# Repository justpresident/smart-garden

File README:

smart-garden
============

Automatic watering system for your garden or home plants

The systems consists of Arduino-compatible AVR microcontroller connected to basic lcd and water pump.

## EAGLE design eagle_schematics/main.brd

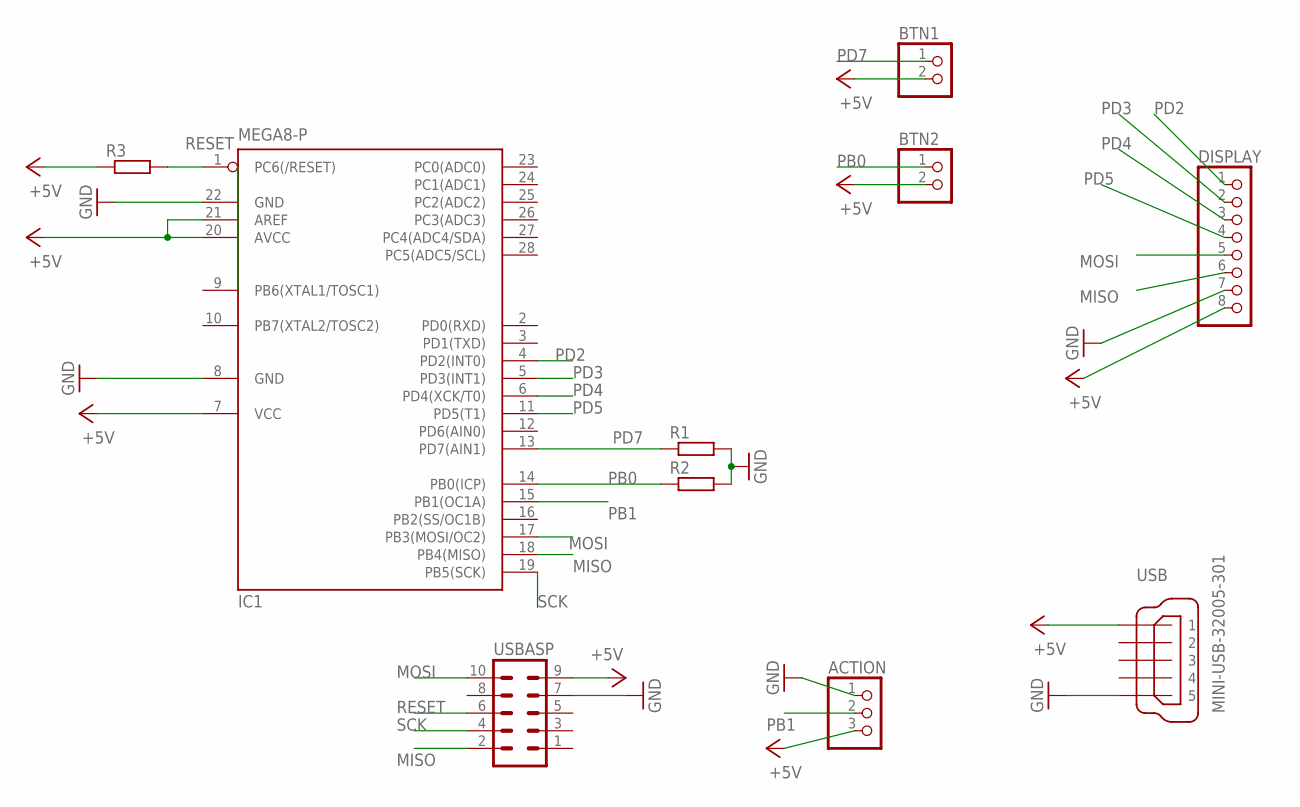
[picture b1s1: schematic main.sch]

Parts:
ACTION: PINHD-1X3; 1X03
BTN1, BTN2: PINHD-1X2; 1X02
DISPLAY: PINHD-1X8; 1X08
IC1: MEGA8-P; DIL28-3
R1, R2, R3: R-EU_0207/7; 0207/7
USB: MINI-USB-32005-301; 32005-301
USBASP: MA05-2

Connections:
+5V: ACTION.3, BTN1.2, BTN2.2, DISPLAY.8, IC1.7 (VCC), IC1.20 (AVCC), IC1.21 (AREF), R3.1, USB.1, USBASP.9
GND: ACTION.1, DISPLAY.7, IC1.8 (GND), IC1.22 (GND), R1.2, R2.2, USB.5, USBASP.7
MISO: DISPLAY.6, IC1.18 (PB4(MISO)), USBASP.2
MOSI: DISPLAY.5, IC1.17 (PB3(MOSI/OC2)), USBASP.10
PB0: BTN2.1, IC1.14 (PB0(ICP)), R2.1
PB1: ACTION.2, IC1.15 (PB1(OC1A))
PD2: DISPLAY.1, IC1.4 (PD2(INT0))
PD3: DISPLAY.2, IC1.5 (PD3(INT1))
PD4: DISPLAY.3, IC1.6 (PD4(XCK/T0))
PD5: DISPLAY.4, IC1.11 (PD5(T1))
PD7: BTN1.1, IC1.13 (PD7(AIN1)), R1.1
RESET: IC1.1 (PC6(/RESET)), R3.2, USBASP.6
SCK: IC1.19 (PB5(SCK)), USBASP.4

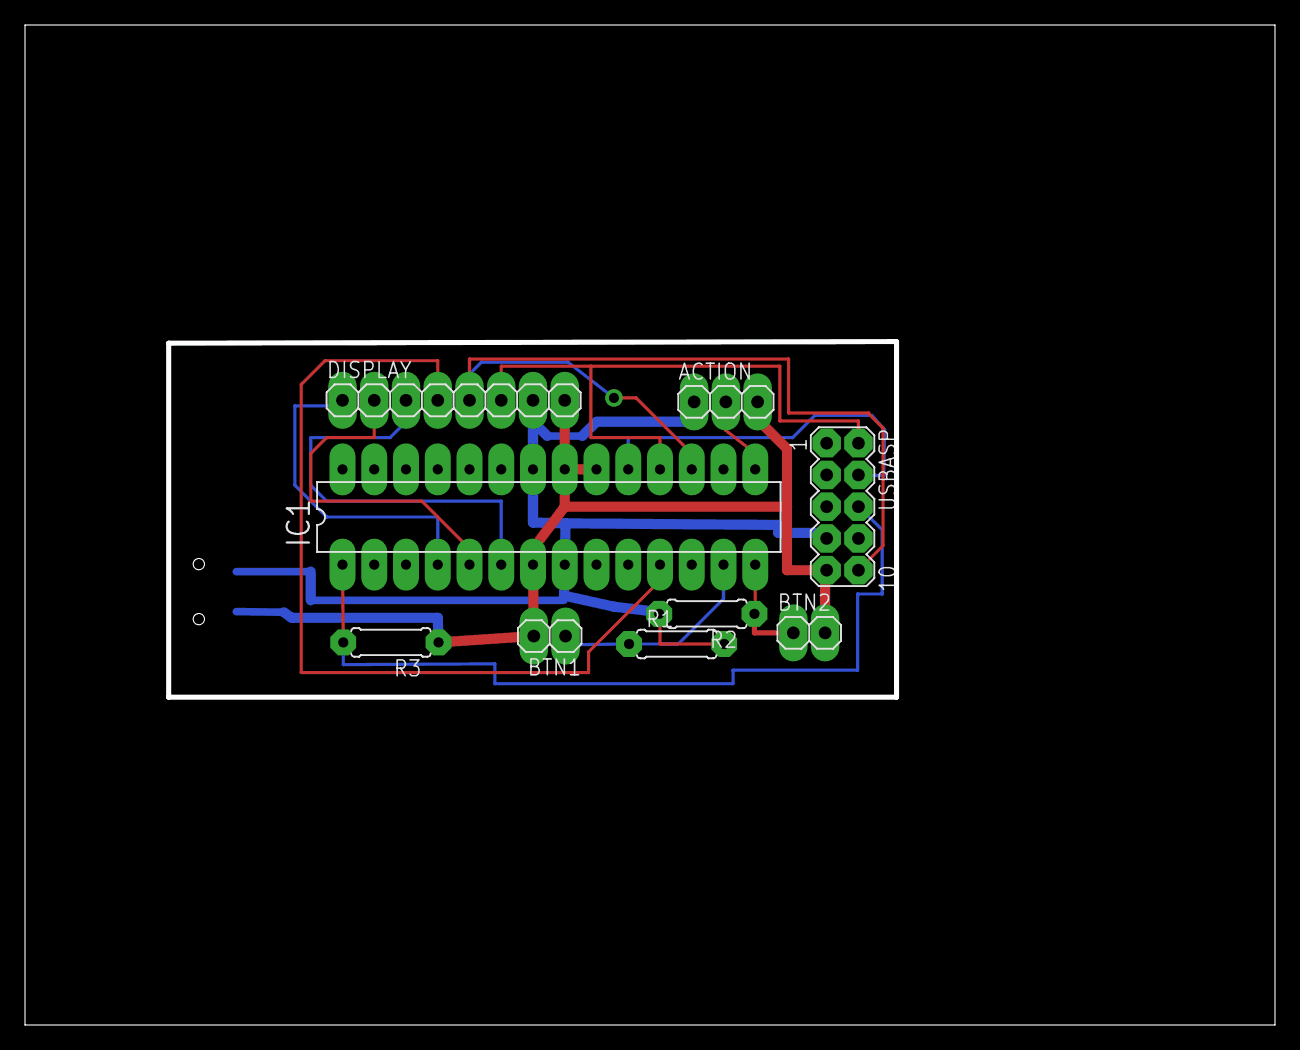
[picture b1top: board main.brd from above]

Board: 2 copper layers, 100.0 x 80.0 mm, 10 parts (1 on the bottom side), 13 nets.

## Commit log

2013-09-11 README updated
2013-09-12 first working system
2013-09-22 save status to EEPROM every hour
2013-09-22 debug removed, micro changes
2014-01-27 eagle schematics added
2014-01-29 fix bug in schematics, change pump pin
